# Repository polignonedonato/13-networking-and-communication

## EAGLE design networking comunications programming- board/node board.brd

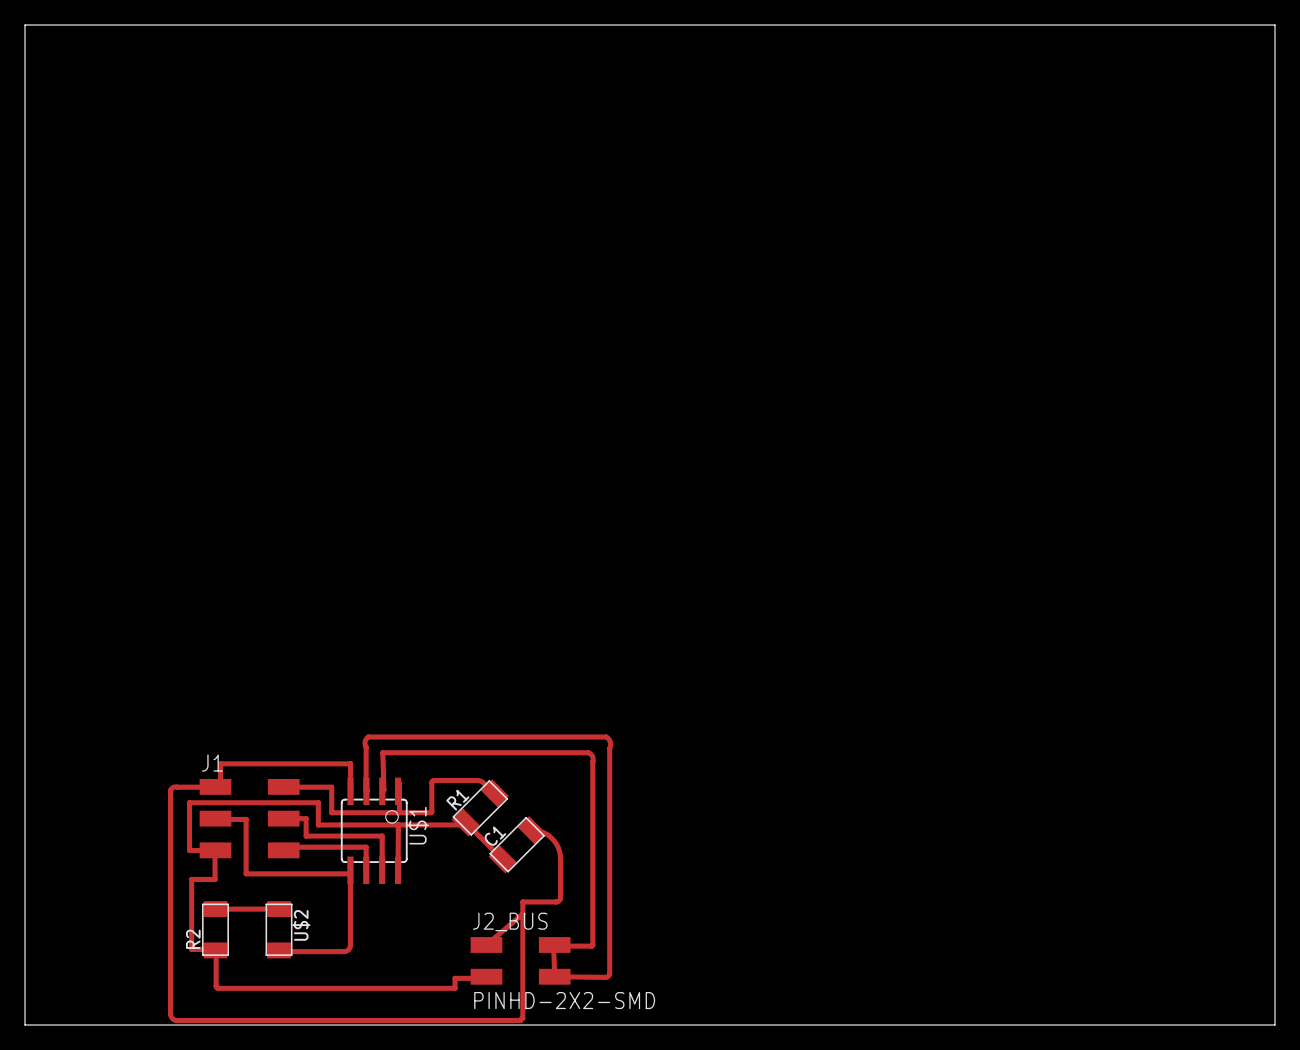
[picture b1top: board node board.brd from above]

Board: 2 copper layers, 100.0 x 80.0 mm, 7 parts (0 on the bottom side), 9 nets.

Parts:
C1: 1uf; C1206FAB
J1: ISP; 2X03SMD
J2_BUS: PINHD-2X2-SMD; 2X02SMD
R1: 10k; R1206FAB
R2: 1k; R1206FAB
U$1: ATTINY45SI; SOIC8
U$2: LEDFAB1206; LED1206FAB

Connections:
A: R2.2, U$2.1
C: J1.3, U$1.5, U$2.2
GND: C1.2, J1.1, J2_BUS.1, U$1.4
MISO: J1.6, U$1.6
RST: J1.2, R1.2, U$1.1
RX: J2_BUS.4, U$1.3
SCK: J1.4, U$1.7
TX: J2_BUS.2, U$1.2
VCC: C1.1, J1.5, J2_BUS.3, R1.1, R2.1, U$1.8

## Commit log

2016-07-12 networking and comunication
    networking and communication
